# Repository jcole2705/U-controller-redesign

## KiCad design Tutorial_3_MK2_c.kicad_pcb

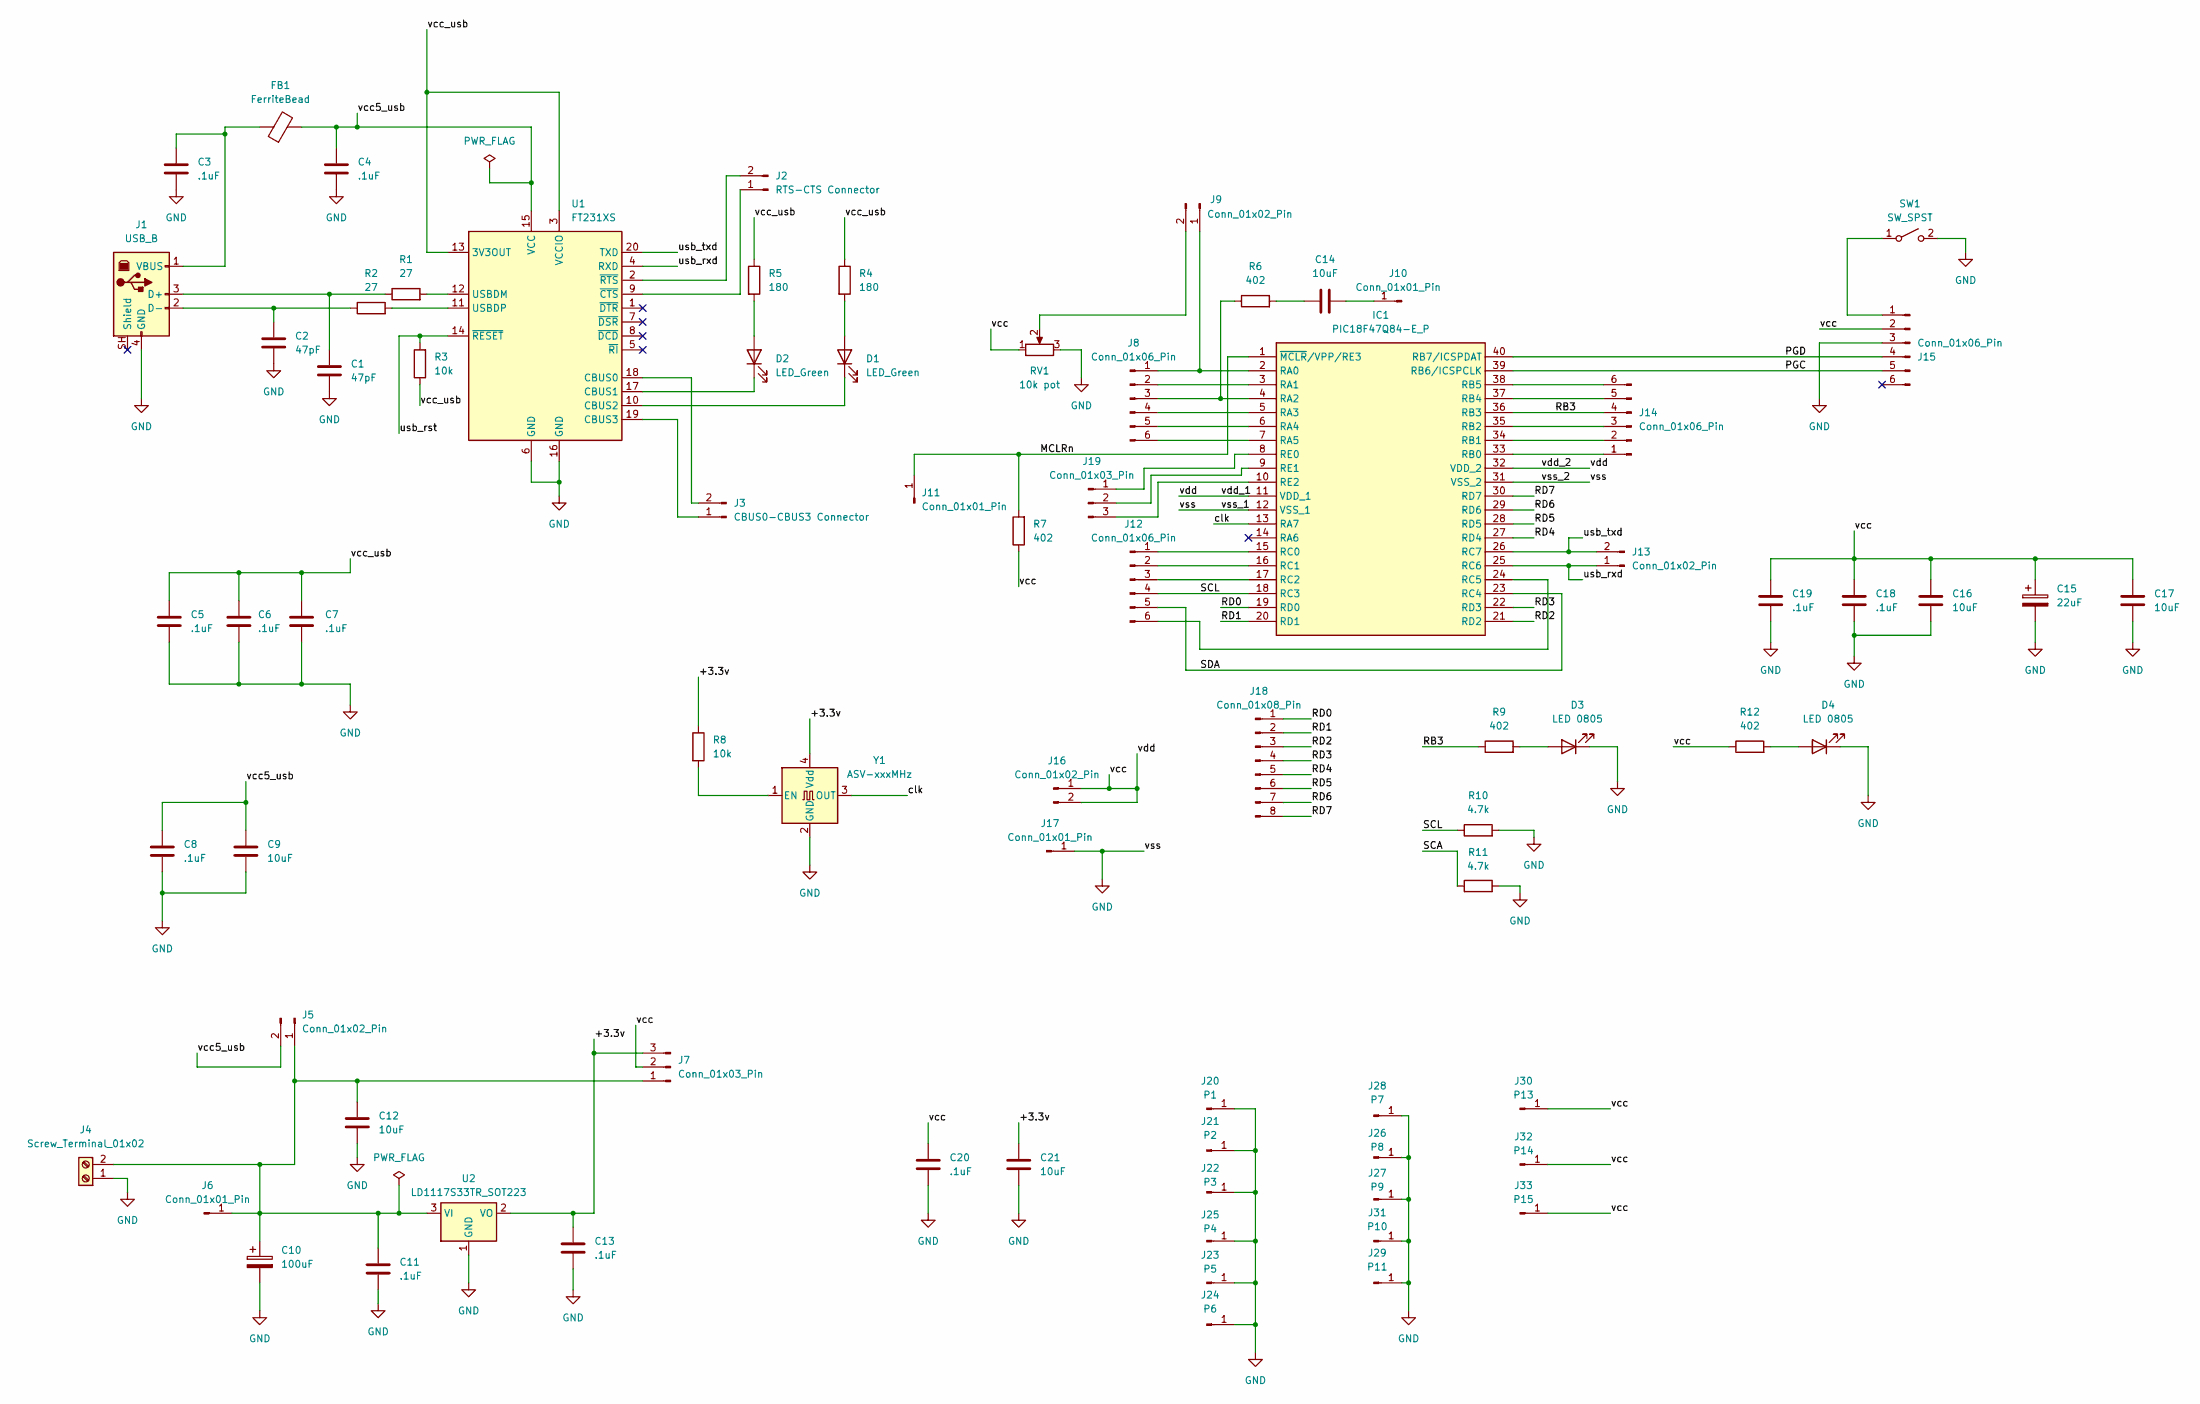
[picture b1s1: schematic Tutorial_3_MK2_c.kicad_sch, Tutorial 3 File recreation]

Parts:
C1, C2: 47pF; C_0201_0603Metric
C3, C4, C5, C6, C7, C8, C11, C13, C18, C19, C20: .1uF; C_0201_0603Metric
C9, C12, C14, C16, C17, C21: 10uF; C_0201_0603Metric
C10: 100uF; C_0201_0603Metric
C15: 22uF; C_0201_0603Metric
D1, D2: LED_Green; LED_D3.0mm
D3, D4: LED 0805; LED_D3.0mm_Clear
FB1: FerriteBead; LairdTech_28C0236-0JW-10
IC1: PIC18F47Q84-E_P; DIP-40_W15.24mm_Socket; Manufacturer_Part_Number PIC18F47Q84-E/P; Mouser Part Number 579-PIC18F47Q84-E/P
J1: USB_B; USB_B_TE_5787834_Vertical
J2: RTS-CTS Connector; PinHeader_1x02_P1.00mm_Vertical
J3: CBUS0-CBUS3 Connector; PinHeader_1x02_P1.00mm_Vertical
J4: Screw_Terminal_01x02; PinHeader_1x02_P1.00mm_Vertical
J5, J9, J13, J16: Conn_01x02_Pin; PinHeader_1x02_P1.00mm_Vertical
J6, J10, J11, J17: Conn_01x01_Pin; PinHeader_1x01_P1.00mm_Vertical
J7, J19: Conn_01x03_Pin; PinHeader_1x03_P1.00mm_Vertical
J8, J12, J14, J15: Conn_01x06_Pin; PinHeader_1x06_P1.00mm_Vertical
J18: Conn_01x08_Pin; PinHeader_1x08_P1.00mm_Vertical
J20: P1; Fiducial_0.5mm_Mask1.5mm
J21: P2; Fiducial_0.5mm_Mask1.5mm
J22: P3; Fiducial_0.5mm_Mask1.5mm
J23: P5; Fiducial_0.5mm_Mask1.5mm
J24: P6; Fiducial_0.5mm_Mask1.5mm
J25: P4; Fiducial_0.5mm_Mask1.5mm
J26: P8; Fiducial_0.5mm_Mask1.5mm
J27: P9; Fiducial_0.5mm_Mask1.5mm
J28: P7; Fiducial_0.5mm_Mask1.5mm
J29: P11; Fiducial_0.5mm_Mask1.5mm
J30: P13; Fiducial_0.5mm_Mask1.5mm
J31: P10; Fiducial_0.5mm_Mask1.5mm
J32: P14; Fiducial_0.5mm_Mask1.5mm
J33: P15; Fiducial_0.5mm_Mask1.5mm
R1, R2: 27; R_0201_0603Metric
R3, R8: 10k; R_0201_0603Metric
R4, R5: 180; R_0201_0603Metric
R6, R7, R9, R12: 402; R_0201_0603Metric
R10, R11: 4.7k; R_0201_0603Metric
RV1: 10k pot; Potentiometer_Vishay_248GJ-249GJ_Single_Vertical
SW1: SW_SPST; SW_DIP_SPSTx01_Piano_10.8x4.1mm_W7.62mm_P2.54mm
U1: FT231XS; SSOP-20_3.9x8.7mm_P0.635mm
U2: LD1117S33TR_SOT223; SOT-223-3_TabPin2
Y1: ASV-xxxMHz; Oscillator_SMD_Abracon_ASV-4Pin_7.0x5.1mm

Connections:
/+3.3v: C13.1, C21.1, J7.3, R8.1, U2.2 (VO), Y1.4 (Vdd)
/MCLRn: IC1.1 (~MCLR/VPP/RE3), J11.1 (Pin_1_1), R7.2
/PGC: IC1.39 (RB6/ICSPCLK), J15.5
/PGD: IC1.40 (RB7/ICSPDAT), J15.4
/RB3: IC1.36 (RB3), J14.4, R9.1
/RD0: IC1.19 (RD0), J18.1
/RD1: IC1.20 (RD1), J18.2
/RD2: IC1.21 (RD2), J18.3
/RD3: IC1.22 (RD3), J18.4
/RD4: IC1.27 (RD4), J18.5
/RD5: IC1.28 (RD5), J18.6
/RD6: IC1.29 (RD6), J18.7
/RD7: IC1.30 (RD7), J18.8
/SCL: IC1.18 (RC3), J12.4, R10.1
/clk: IC1.13 (RA7), Y1.3 (OUT)
/usb_rst: R3.2, U1.14 (~RESET)
/usb_rxd: IC1.25 (RC6), J13.1, U1.4 (RXD)
/usb_txd: IC1.26 (RC7), J13.2, U1.20 (TXD)
/vcc: C15.1, C16.1, C17.1, C18.1, C19.1, C20.1, IC1.11 (VDD_1), IC1.32 (VDD_2), J7.2, J15.2, J16.1, J16.2, J30.1, J32.1, J33.1, R7.1, R12.1, RV1.1
/vcc5_usb: C4.1, C8.1, C9.1, FB1.2, J5.2, U1.15 (VCC)
/vcc_usb: C5.1, C6.1, C7.1, R3.1, R4.1, R5.1, U1.3 (VCCIO), U1.13 (3V3OUT)
GND: C1.2, C2.2, C3.2, C4.2, C5.2, C6.2, C7.2, C8.2, C9.2, C10.2, C11.2, C12.2, C13.2, C15.2, C16.2, C17.2, C18.2, C19.2, C20.2, C21.2, D3.1 (K), D4.1 (K), IC1.12 (VSS_1), IC1.31 (VSS_2), J1.4 (GND), J4.1, J15.3, J17.1 (Pin_1_1), J20.1, J21.1, J22.1, J23.1, J24.1, J25.1, J26.1, J27.1, J28.1, J29.1, J31.1, R10.2, R11.2, RV1.3, SW1.2 (B), U1.6 (GND), U1.16 (GND), U2.1 (GND), Y1.2 (GND)
unnamed: C14.1, R6.2
unnamed: D1.2 (A), R4.2
unnamed: D1.1 (K), U1.10 (CBUS2)
unnamed: D2.2 (A), R5.2
unnamed: D2.1 (K), U1.17 (CBUS1)
unnamed: D3.2 (A), R9.2
unnamed: D4.2 (A), R12.2
unnamed: IC1.2 (RA0), J8.1, J9.1
unnamed: IC1.3 (RA1), J8.2
unnamed: IC1.4 (RA2), J8.3, R6.1
unnamed: IC1.5 (RA3), J8.4
unnamed: IC1.6 (RA4), J8.5
unnamed: IC1.7 (RA5), J8.6
unnamed: IC1.33 (RB0), J14.1
unnamed: IC1.34 (RB1), J14.2
unnamed: IC1.35 (RB2), J14.3
unnamed: IC1.37 (RB4), J14.5
unnamed: IC1.38 (RB5), J14.6
unnamed: IC1.15 (RC0), J12.1
unnamed: IC1.16 (RC1), J12.2
unnamed: IC1.17 (RC2), J12.3
unnamed: IC1.24 (RC5), J12.6
unnamed: IC1.8 (RE0), J19.1
unnamed: IC1.9 (RE1), J19.2
unnamed: IC1.10 (RE2), J19.3
unnamed: C1.1, J1.3 (D+), R1.1
unnamed: C2.1, J1.2 (D-), R2.1
unnamed: C3.1, FB1.1, J1.1 (VBUS)
unnamed: J2.1, U1.9 (~CTS)
unnamed: J2.2, U1.2 (~RTS)
unnamed: J3.1, U1.19 (CBUS3)
unnamed: J3.2, U1.18 (CBUS0)
unnamed: C10.1, C11.1, C12.1, J4.2, J5.1, J6.1 (Pin_1_1), J7.1, U2.3 (VI)
unnamed: J9.2, RV1.2
unnamed: C14.2, J10.1 (Pin_1_1)
unnamed: J15.1, SW1.1 (A)
unnamed: R1.2, U1.12 (USBDM)
unnamed: R2.2, U1.11 (USBDP)
unnamed: R8.2, Y1.1 (EN)

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
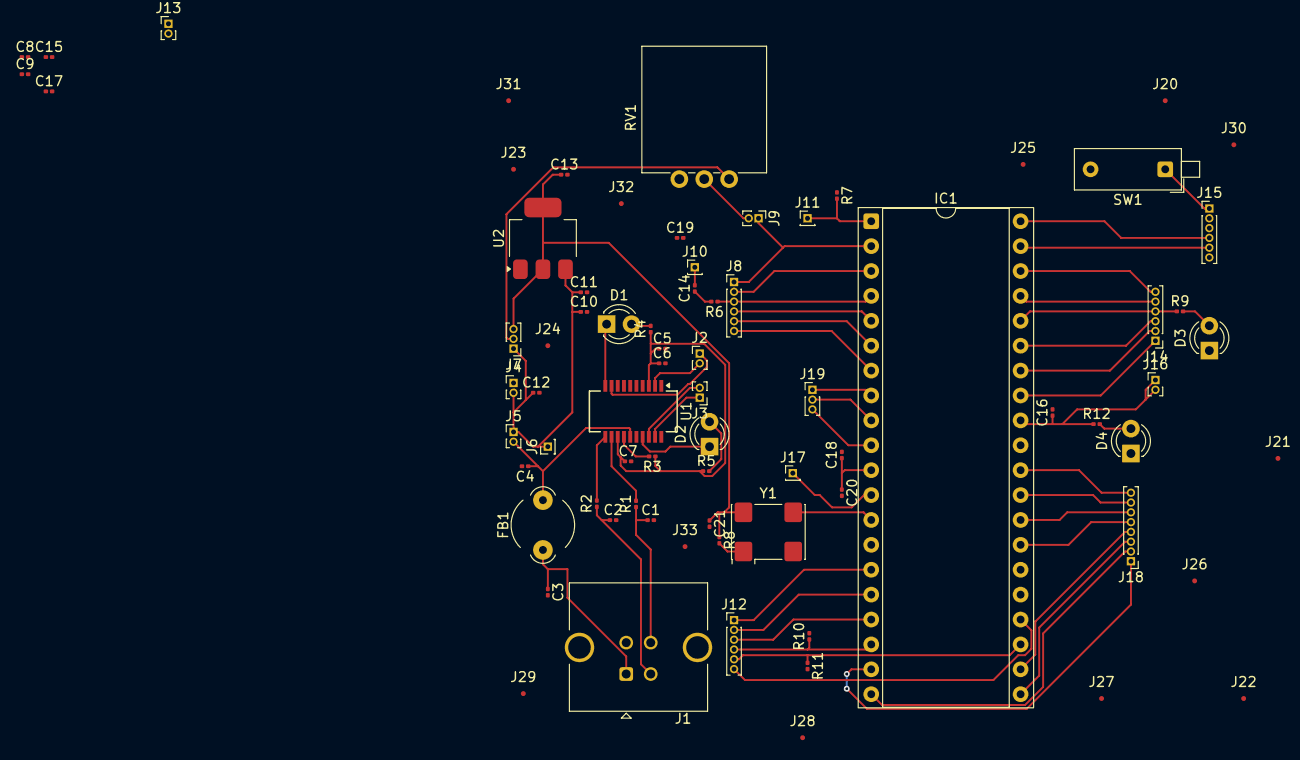
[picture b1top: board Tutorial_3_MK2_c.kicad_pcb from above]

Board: 2 copper layers, 77 parts (0 on the bottom side), 62 nets.
